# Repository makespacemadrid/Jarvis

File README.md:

# Jarvis
Jarvis (En homenaje al personaje de Marvel) es un proyecto creado por los usuarios de Makespace Madrid para domotizar y automatizar distintos aspectos de dicho espacio.

Se basa en un diseño modular que permite hacerlo escalable, de forma que inicialmente será un diseño simple destinado a realizar tareas rutinarias y monótonas del local (apagado de luces, apagado de ordenadores, control y monitorización de la calidad del aire...) y poco a poco podrá ampliarse a tareas cada vez más sofisticadas y complejas.

Pese a estar siendo desarrollado para un lugar concreto es fácilmente portable a otro tipo de ambientes (locales de trabajo, viviendas... )

****Cómo colaborar:****

1- Haz un fork del repo y aprende a usar git a nivel basico:

    https://github.com/makespacemadrid/Jarvis/wiki/Git-b%C3%A1sico

2- Monta el entorno de desarollo

    https://github.com/makespacemadrid/Jarvis/wiki/Montando-el-entorno-de-desarrollo

3- Si en el camino encuentras algo que falta o esta mal explicado mejoralo en la wiki para el proximo ;)

4-Echa un ojo a los issues y encuentra alguna tarea con la que te gustaria colaborar:

    https://github.com/makespacemadrid/Jarvis/issues

5-Pásate por MakeSpace y habla con un miembro del equipo de Jarvis para tutela/materiales, el Jueves suele ser un dia propicio.

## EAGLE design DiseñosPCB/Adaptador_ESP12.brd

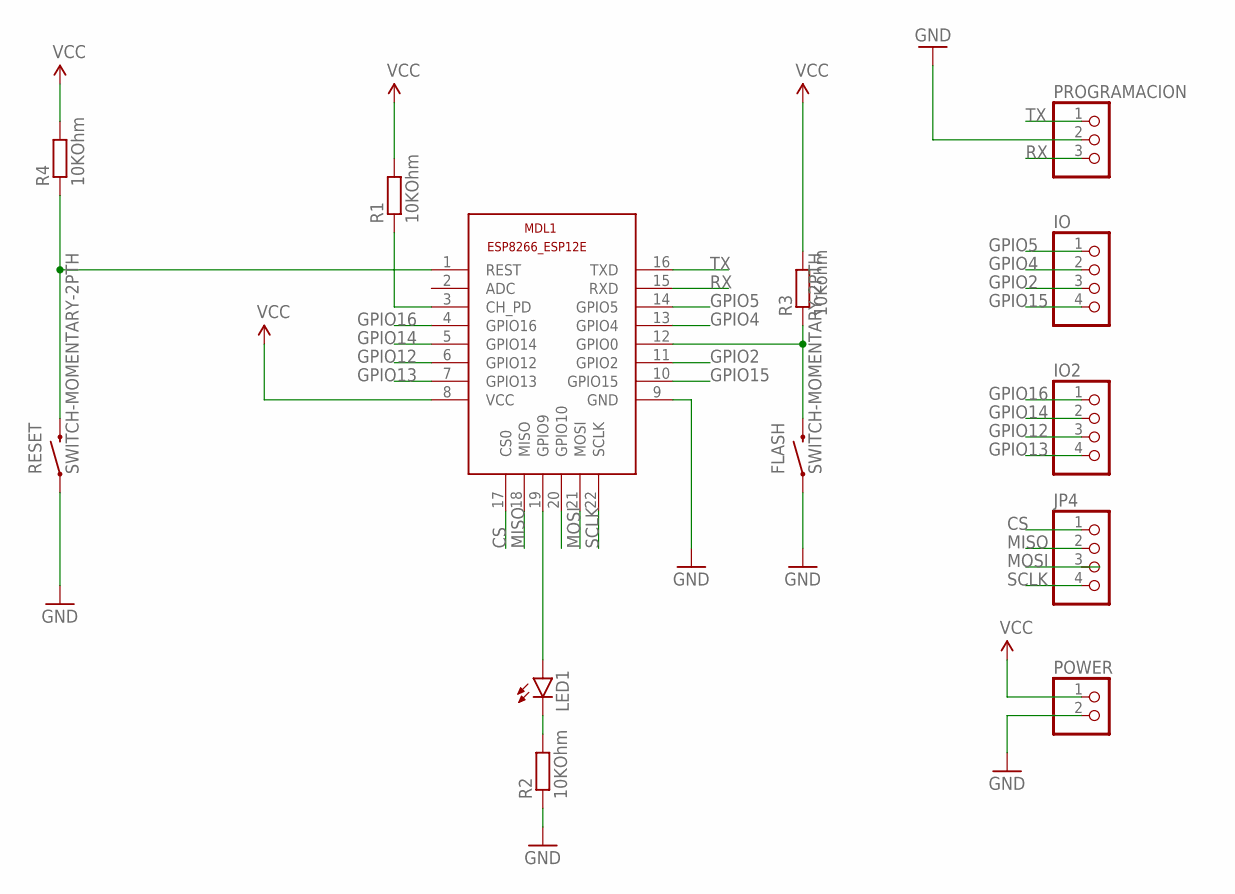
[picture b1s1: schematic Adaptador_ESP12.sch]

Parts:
FLASH: SWITCH-MOMENTARY-2PTH; TACTILE-PTH
IO, IO2: PINHD-1X4; 1X04
JP4: PINHD-1X4; 1X04
LED1: LED-3MM-NO_SILK; LED3MM-NS
MDL1: ESP8266-12EESP8266-ESP12E; ESP8266-ESP12E
POWER: PINHD-1X2; 1X02
PROGRAMACION: PINHD-1X3; 1X03
R1, R2, R4: 10KOhm; 0207/7
R3: 10Kohm; 0207/7
RESET: SWITCH-MOMENTARY-2PTH; TACTILE-PTH

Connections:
CS: JP4.1, MDL1.17 (CS0)
GND: FLASH.1, MDL1.9 (GND), POWER.2, PROGRAMACION.2, R2.1, RESET.1
GPIO2: IO.3, MDL1.11 (GPIO2)
GPIO4: IO.2, MDL1.13 (GPIO4)
GPIO5: IO.1, MDL1.14 (GPIO5)
GPIO12: IO2.3, MDL1.6 (GPIO12)
GPIO13: IO2.4, MDL1.7 (GPIO13)
GPIO14: IO2.2, MDL1.5 (GPIO14)
GPIO15: IO.4, MDL1.10 (GPIO15)
GPIO16: IO2.1, MDL1.4 (GPIO16)
MISO: JP4.2, MDL1.18 (MISO)
MOSI: MDL1.21 (MOSI)
unnamed: FLASH.3 (2), MDL1.12 (GPIO0), R3.1
unnamed: MDL1.1 (REST), R4.1, RESET.3 (2)
unnamed: MDL1.3 (CH_PD), R1.1
unnamed: LED1.K (C), R2.2
unnamed: LED1.A, MDL1.19 (GPIO9)
RX: MDL1.15 (RXD), PROGRAMACION.3
SCLK: JP4.4, MDL1.22 (SCLK)
TX: MDL1.16 (TXD), PROGRAMACION.1
VCC: MDL1.8 (VCC), POWER.1, R1.2, R3.2, R4.2

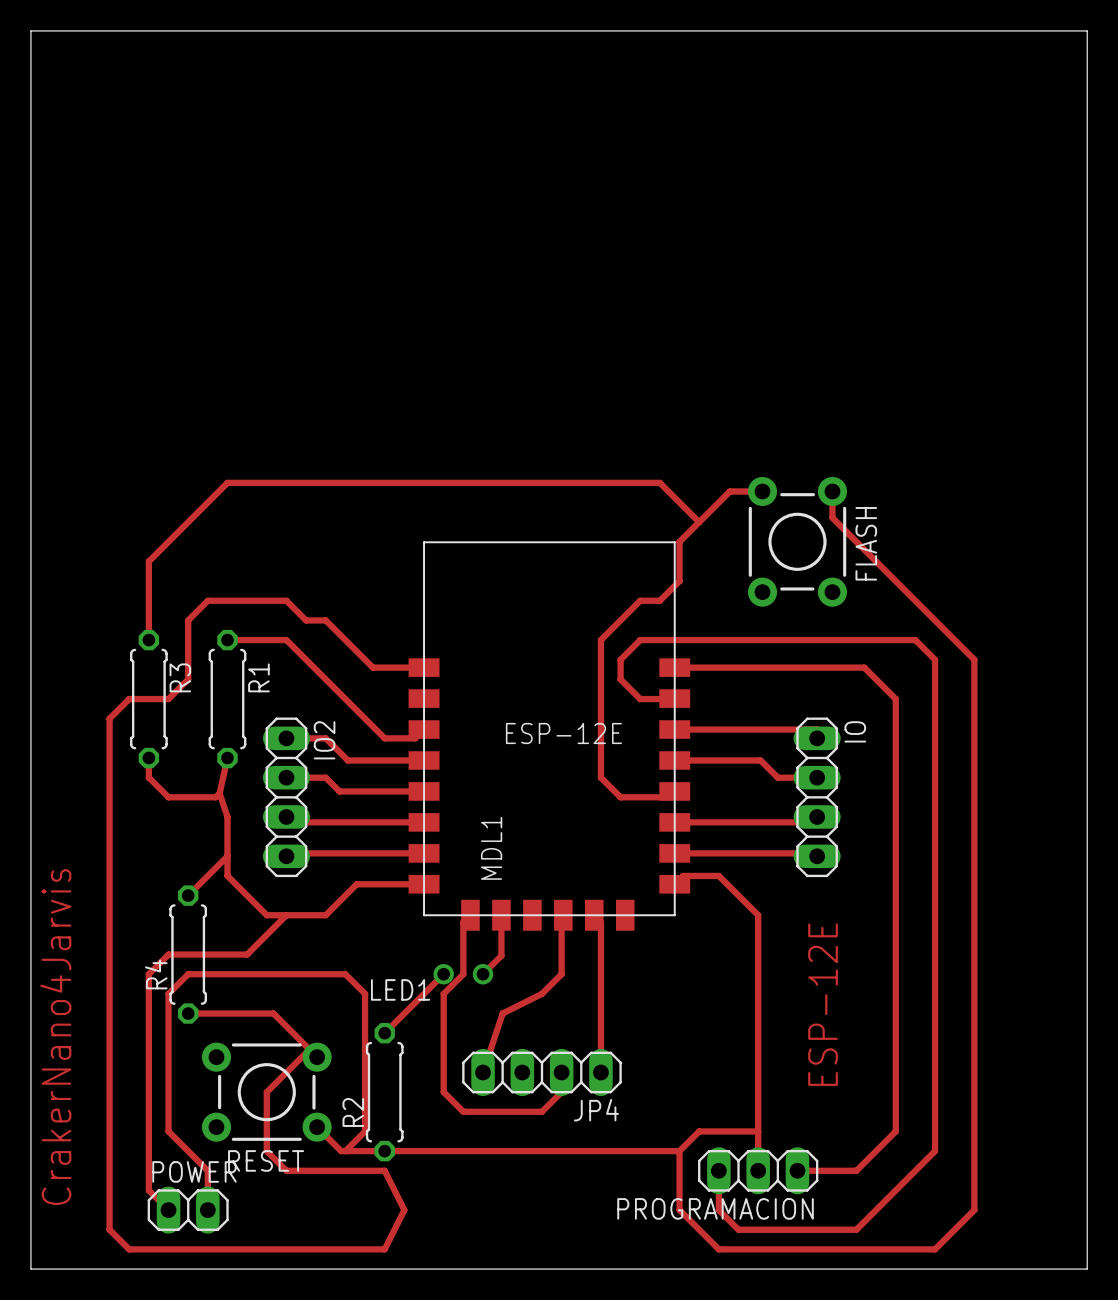
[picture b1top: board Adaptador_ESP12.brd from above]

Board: 2 copper layers, 68.2 x 80.0 mm, 13 parts (0 on the bottom side), 20 nets.

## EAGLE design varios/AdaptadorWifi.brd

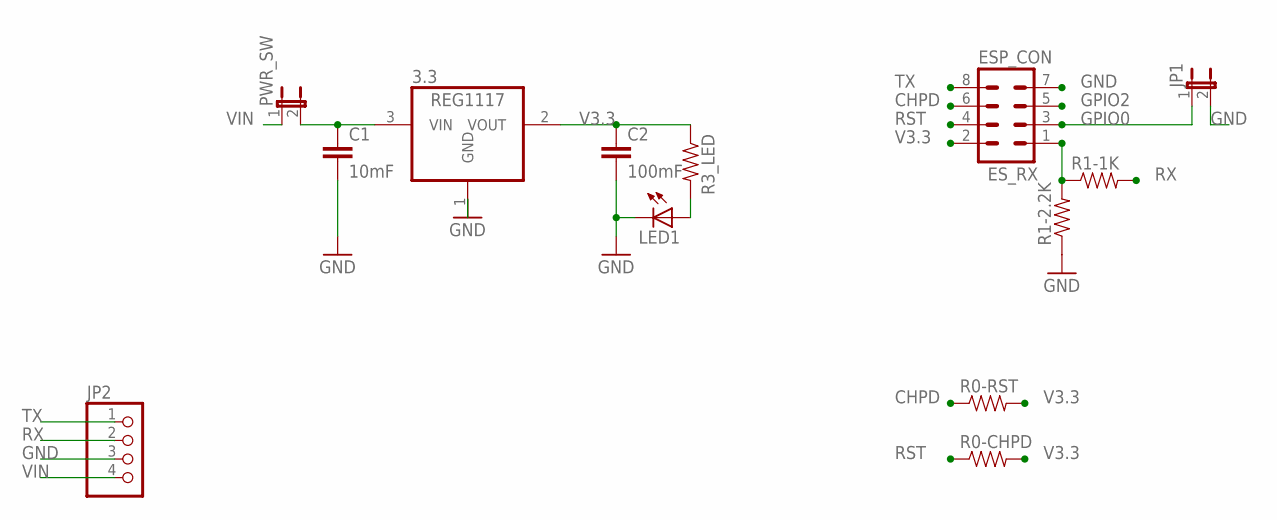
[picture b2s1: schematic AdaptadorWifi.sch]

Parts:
3.3: REG1117; SOT223
C1: 10mF; 1206
C2: 100mF; 1206
ESP_CON: MA04-2
JP1: JUMPER-2PTH; 1X02
JP2: PINHD-1X4/90; 1X04/90
LED1: LED1206; LED-1206
PWR_SW: JUMPER-2PTH; 1X02
R0-CHPD, R0-RST, R1-1K, R1-2.2K, R3_LED: RESISTOR1206; 1206

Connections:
CHPD: ESP_CON.6, R0-RST.1
ES_RX: ESP_CON.1, R1-1K.1, R1-2.2K.2
GND: 3.3.1 (GND), C1.2, C2.2, ESP_CON.7, JP1.2, JP2.3, LED1.C, R1-2.2K.1
GPIO0: ESP_CON.3, JP1.1
GPIO2: ESP_CON.5
unnamed: LED1.A, R3_LED.2
unnamed: 3.3.3 (VIN), C1.1, PWR_SW.2
RST: ESP_CON.4, R0-CHPD.1
RX: JP2.2, R1-1K.2
TX: ESP_CON.8, JP2.1
V3.3: 3.3.2 (VOUT), C2.1, ESP_CON.2, R0-CHPD.2, R0-RST.2, R3_LED.1
VIN: JP2.4, PWR_SW.1

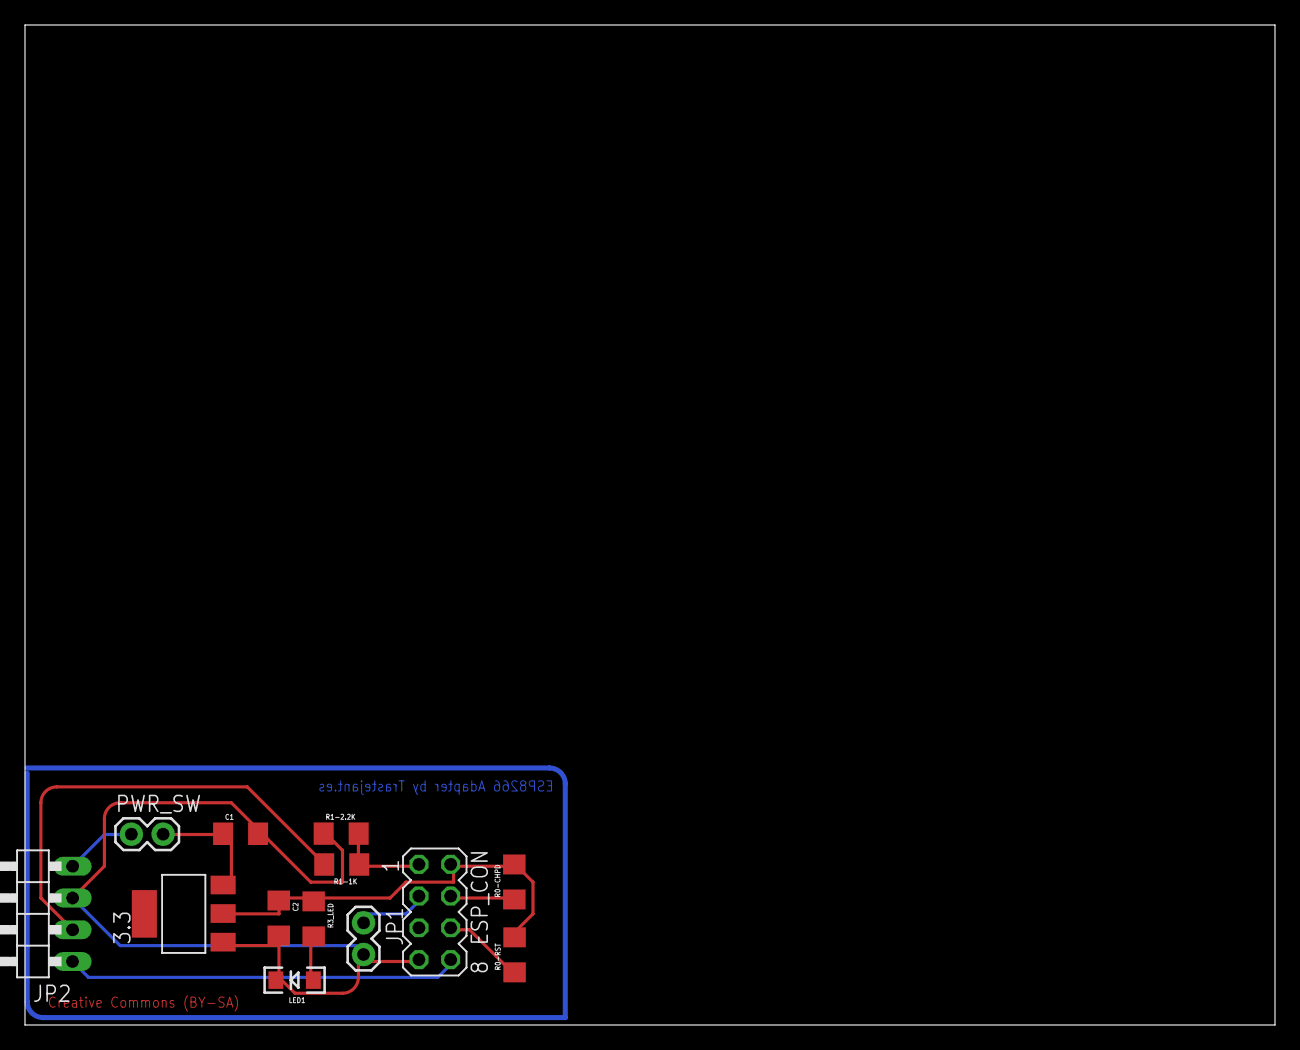
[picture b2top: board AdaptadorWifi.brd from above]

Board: 2 copper layers, 100.0 x 80.0 mm, 13 parts (0 on the bottom side), 11 nets.

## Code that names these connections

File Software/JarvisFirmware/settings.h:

#ifndef FIRMWARESETTINGS
#define FIRMWARESETTINGS

#ifndef ESP8266
#ifndef __AVR_ATmega2560__
//buscar otra etiqueta que descarte el arduino
//Por alguna razon no soy capaz de hacerlo funcionar con #ifdef QT
    #include <QObject>
    typedef quint16 uint16_t;
    typedef quint8 uint8_t;
#endif
#endif

enum jarvisModules
{// el orden de los elementos tiene que coincidir con el de la ventana de configuracion del lado del server
 // Añadir elementos por el final, no reordenarlos.
    unknownModule,
    unConfiguredModule,
    simpleSwitchModule,
    makeSwitchModule,
    airQualityModule,
    simplePowerControlModule,
    advancedPowerControlModule,
    coffeeMakerModule,
    ledNotificationPanelModule,
    ledPanelModule,
    testNodeModule,
    termometroNodeModule,
    doorControlModule
};

struct settingList
{//Configuracion por defecto (Factory)
  //Datos de conexion
  jarvisModules moduleType    = unConfiguredModule;
  char          id[20]          = "Configureme";
  char          wifiESSID[25]   = "ConfigureMe";
  char          wifiPasswd[25]  = "configureme";
  bool          wifiAPMode      = true;
  char          remoteHost[25]  = "Jarvis";
  uint16_t      remotePort      = 31416;
  uint16_t      localPort       = 31416;
  uint16_t      updateInterval  = 25;

  int8_t            alivePin            =   2;
  int8_t            piezoPin            =  -1;
  int8_t            ledStripPin         =  13;
  float             ledStripBrightness  =   0.1f;
  uint16_t          ledCount            =   3;
  uint8_t           ledMatrixFirstLed   =   0;
  uint8_t           ledMatrixCols       =   16;
  uint8_t           ledMatrixRows       =   16;
  bool              ledMatrixZigZag     =   true;
  bool              ledMatrixMirror     =   false;


  int8_t           buttonPins[10]      = {  16,  -1,  -1,  -1,  -1,  -1,  -1,  -1,  -1,  -1};
  int8_t           tempSensorPins[10]  = {   5,  -1,  -1,  -1,  -1,  -1,  -1,  -1,  -1,  -1};
  int8_t           relaypins[10]       = {  12,  -1,  -1,  -1,  -1,  -1,  -1,  -1,  -1,  -1};

  uint16_t          magicNumber            = 31415;

  /**
Tabla de correspondencia de pines nodemcu arduino
0 [*]  GPIO16  
1  GPIO5 
2  GPIO4
3  GPIO0
4  GPIO2
5  GPIO14 (SPI CLK)    
6  GPIO12 (SPI MISO)   
7  GPIO13 (SPI MOSI)   
8  GPIO15 (SPI CS)
9  GPIO3 (UART RX)
10 GPIO1 (UART TX)
11 GPIO9
12 GPIO10
A0 17
**/  

//Pineado por defecto de los nodos ESP8266
//    int   ledStripPin            =  4; //makeswitch
//    int   ledStripPin            =  13; // LedPanel /coffeemaker
//    DHT    makeswitch  5
//    dht MMMtermimetro  2


};

#endif

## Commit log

2015-05-18 Primera idea para el diseño del modulo "MakeSwitch"
2015-05-18 Actualizado readme desde el del repo de Trastejant
2015-05-21 Script para apagar equipos
2015-05-21 Sketch (Provisional) de los modulos de calidad del aire
2015-05-22 Mejora lectura del sensor MQ135
2015-05-23 Incluida información básica de git
2015-05-23 debugger mode, disable mode
2015-05-25 Almacentamiento de informacion y sistema de alarmas
2015-05-25 asignacion dinamica de la MAC
2015-05-26 Interfaz Jarvis
2015-05-26 Modo autonomo implementado
2015-05-27 Abstraccion de metodos y funciones
2015-05-28 Libreria para realizar debuggeo del modulo
2015-05-28 nuevos metodos de manejo de datos
2015-06-03 Tapa para los modulos de control de enchufes con conmutador
2015-06-03 Compatibilidad inversa con los IDE Arduino de las librerias
2015-06-07 Script de arranque de Lua para esp8266
2015-06-09 Libreria para controlar la cerradura de la puerta interior.
2015-06-11 Mejora de la libreria para deteccion de incendios
2015-06-12 Rectificadas tolerancias del cubre-modulos para enchufes
2015-08-03 Carcasa para el modulo de calidad del aire
2015-08-22 Adaptador para los ESP2866
2015-09-30 Clases y definiciones para el programa de control de los enchufes
2015-10-02 mas codigo para los sensores
2015-10-04 Inicio del modulo de comunicaciones. codigo c y pruebas en lua para el puente serie
2015-10-07 Mas codigo para los sensores.
    Probado el codigo de los leds
2015-10-09 Mas codigo y reorganizacion del mismo
2015-10-09 Trabajos en el modulo de comunicacion, wtf variados.
2015-10-13 Mejora del parseador
2015-10-13 arreglado el bug del puerto de comunicaciones.
2015-10-14 Primeras pruebas con el interface web en el esp Modulo de comunicacion esclavo
2015-10-18 refactorizacion del parseador para poder reutilizarlo tanto en los modulos como en el cerebro
2015-10-20 refactorizacion completa
2015-10-22 refactorizacion del codigo.
    despues de la cagada de borrar la carpeta de trabajo sin haber actualizado le repo en dos dias se ha refactorizado el codigo para integrarlo todo en la clase jarvisModule.
    En el camino he reimplementado gran parte de los cambios que se han perdido, aunque todavia queda bastante para dejarlo en el estado que estaba esta mañana.
2015-11-26 update?
2015-11-27 Reorganizacion del repo
2015-11-27 Inicio de JarvisServer
    Despliege de clases para el servidor
2015-11-29 MakeSwitch V2
2015-12-01 pequeñas correcciones
2015-12-04 Carcasa MakeSwitch cortada a la mitad
2015-12-06 Jarvis firmware 0.6
    Trabajos variados en el firmware para la implementacion en el primer modulo.
    -Movida toda la parte de parseo de protocolo a la clase communicationModule, desde el parseo se llaman a interfaces virtuales que implementa el jarvisModule.
    -Creados interfaces para sensores y actuadores, que pueden emitir eventos y recibir acciones.
    -Ahora el modulo de jarvis contiene arrays(vectores) de sensores y actuadores, la idea es que los 'modulos finales lo hereden y añadan sus sensores y actuadores a los arrays de sensores/actuadores pa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
    (Implementacion del makeswitch como ejemplo)
    -Reformado el codigo de los led, y hecho sensor.
2015-12-08 animaciones para los leds
2015-12-11 Refactorizacion del codigo: -Sensores y actuadores unidos en una unica interfaz nodeComponent -Mejoras en los objetos de los led -Creado nuevo tipo de objeto para controlar la cafetera -Limpieza por 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
    Vuelve a compilar para el arduino Nano!! eso si, con calzador(99%)
2015-12-14 Aplicacion de test para los Nodos
    - Mejoras de codigo por aqui y por alla para hacer la integracion.
    Funciones:
    - Señalizacion de los eventos.
    - Visualizacion de las acciones, y posibilidad de actuar sobre las mismas.
    - Graficas con las lecturas de los sensores
    - Consola
2015-12-28 Mejoras aqui y alla:
    (cambios de los que me acuerdo)
    Jarvis Firmware
    - Terminados de implementar los metodos de lectura de componentes a traves de interfaz
    Cambios en la forma de lectura, ahora se pueden consultar los sensores a traves de las acciones, generandose un evento de lectura.
    Paralelamente se puede activar un modo de lectura periodica para consultar los sensores a alta velocidad sin riesgo de petar el buffer de entrada con las solicitudes.
    -Nuevo tipo de nodo ledPanel para controlar una matriz led de 16*16
2015-12-29 actualizacion previa al merge
2015-12-29 Plantilla de nodeComponent y JarvisNode
2016-01-03 Implementacion para el reloj de tiempo real PCB adaptadores para los ESP12E
2016-01-10 -Ampliación del modulo coffeeMaker
    Ahora puede hacer cae :)
    -Mejoras en el manejo de los leds
    Mas efectos.
    -Cambio en la estructura del jarvisNode, ahora el nodo hereda tambien un nodeComponent.
    Jugando con las implementaciones de los nodos estaba econtrando problemas con la gestion de eventos, pues al final el nodo acaba funcionando como un 'supercomponente de componentes' que necesita acce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
    p.e.: el modulo de la cafetera para reaccionar la accion "MAKE_COFFEE" necesita poder leer la temperatura del sensor y operar sobre el rele(ambos componentes aparte).
2016-01-13 Configurado git ignore para ignorar los pro.user de qt
2016-01-14 Mejoras en el modulo coffeeMaker e implementacion dummy de un termistor ntc100k
2016-01-14 Actualizacion del makeswitch al nuevo formato de modulo
2016-01-14 Trabajos en el modulo coffeemaker
2016-01-14 Fichero de pro.user
2016-01-17 modificado el patron de gitignore para que ignore todos los directorios que empiecen con build-
2016-01-17 arreglado gitignore
2016-01-17 Mejoras varias cliente/servidor: -validacion del cliente y el servidor, ahora ambos se saludan para verificar que estan hablando con lo que esperan hablar. -añadido sensor de temperatura tmp36 -Reorg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
2016-01-19 Modulo de termometro
2016-01-19 Eliminado el metodo sendEvent includido el metodo jarvisConnected
2016-01-20 Pineado correcto para los modulos de termometro
2016-01-21 Mejoras en la aplicacion movil
2016-01-22 Mejoras en la matriz led.
    Ahora contiene un array de dos dimensiones con la geometria del display
    m_matrix[x[y]
2016-01-22 Comentado #define que puede dar problemas.
    Para que el qt creator haga completado de codigo en la parte especifica del esp en el communication.h uso un define para habilitar la etiqueta ,la ultima vez me la deje puesta y podria hacer fallar l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
2016-01-24 Añadido actualizador web y repondedor mdns
    Ambos estan integrados en la ultima version de la integracion de arduino.
    El webflash funciona el 50% de las veces... el 25% te deja el esp 'brickeado' y hay que reprogramar por serie
2016-01-26 Mejoras para el panel de leds nodo/cliente/testapp.
    Cambios en el metodo de transmision, nueva accion A_DISPLAY que manda los pixeles a la pantalla en formato x,y,r,g,b .... nx,ny,nr,ng,nb
    Mejoras en la ventana de seleccion de imagen
    etc....
2016-01-31 Informar de la ip al conectarse
    Ahora se escupe la direccion ip despues de conectar, asi no hay que reiniciar para saber la ip.
    Ahora la red de autoconfiguracion lleva el id del chip en el nombre de la red para evitar confusion entre varios dispositivos.
2016-02-02 update : trabajos en jarvisServer
2016-02-06 Trabajos en el server / app de test
2016-02-09 Mecanismo de conexion automatica al servidor.
    -Gestion de la conexion/reconexion con el servidor. host/port se cargan desde la EEPROM.
2016-02-09 Mejoras en el mecanismo de autoconexion/reconexion
2016-02-09 Mecanismo de conexion/reconexion server-side
    Refactorizacion del servidor para adaptarse a como funciona qt5
2016-02-10 mas cambios que me habia dejado en el mergue
2016-02-22 Mejoras variadas en el firmware/server (Incluido pero no limitado a ....) Firmware: - bugs del piezo - Mejoras en los leds, ahora responden a la accion DIMM para establecer su brillo(independiente de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
    Server
    - Ventanas varias para el reproductor rtttl y configuracion del wifi del nodo
    - Mejoras en el mecanismo de recoñexion de los nodos
2016-02-26 -Mejoras en el mecanismo de conexion accion-evento server-side -Arreglado el pineado el ledPanelNode
2016-03-06 pequeño fix de operadores
2016-03-18 udpate
    changelog en el proximo commit
2016-03-20 -Manejo de settings y eeprom. -Transmision de la configuracion por la red. -Actualizacion del los objetos del servidor para manejar las nuevas opciones. -Mejoras en el panel de leds
2016-03-20 Watchdog externo
2016-03-21 fixes
2016-03-21 Hola Jarvis!
    Sistema de conexion de eventos y acciones funcional :D
    inicialmente las habia llamado connecions aunque creo que rules va a ser un nombre mas claro.
    De momento he empezado a cambiar lo nuevo a rules y ya cambiare los viejos nombres otro dia
2016-03-23 Añadida etiqueta con el pin correspondiente al A0 del nodeMCU
2016-03-24 actualizacion del repo. Mejoras en el interfaz grafico; Poder borrar los nodos para forzar la reconexion/reconfiguracion. Ahora mismo tiene un bug cuando se activa una regla que tenga como destino el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
2016-03-25 Fixes variados -Posible race-condition en los dispositivos con muchos leds en los que era posible que la conn wifi se estableciera antes de terminar de encender todos los leds. -Desregistrar los comp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
2016-03-26 -Terminada ventana de configuracion de reglas -retoques en los widgets -arreglo de bugs
2016-03-26 Añadido estilo a los groupbox de la app de test
2016-03-27 Mejoras para la matriz de leds. -Enesimo intento de ahorrar algo de memoria en el proceso de copiar los datos desde el parseador hasta la matriz de leds. -Mejoras en el widget de envio de jpgs
2016-03-29 conexion de reglas con argumentos
2016-03-30 trabajos en el subsistema de leds
2016-03-30 inicio de integracion del spifs + interfaz web para cargar ficheros
2016-03-31 sync
2016-04-04 -Somera inplementacion de la flash integrada SPIFFS -Carga de imagenes desde la flash para los paneles led -Generador de ficheros de imagen en la app de test
2016-04-04 Imagenes para el panel Mejorada la carga desde SPIFFS Añadida configuracion para la matriz de leds a los settings.
2016-04-05 retoques de imagen
2016-05-04 Mejoras en la carga de imagenes. Aplicacion separada para generar/visualizar los archivos de imagen.
    Se arrastran un par de bugs en la visualizacion del panel y en la app de visualizacion.
2016-05-04 Nodo para el control de la puerta
2016-05-08 Almacenamiento basico de reglas
2016-05-19 actualizacion
2016-11-22 carga y salvado de las reglas
2016-11-23 Fixed saving and loading rules on the server

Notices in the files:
varios/AdaptadorWifi.brd:
Creative Commons (BY-SA)
parts and their libraries:
SparkFun-Electromechanical: Licensing: Creative Commons ShareAlike 4.0 International - https://creativecommons.org/licenses/by-sa/4.0
